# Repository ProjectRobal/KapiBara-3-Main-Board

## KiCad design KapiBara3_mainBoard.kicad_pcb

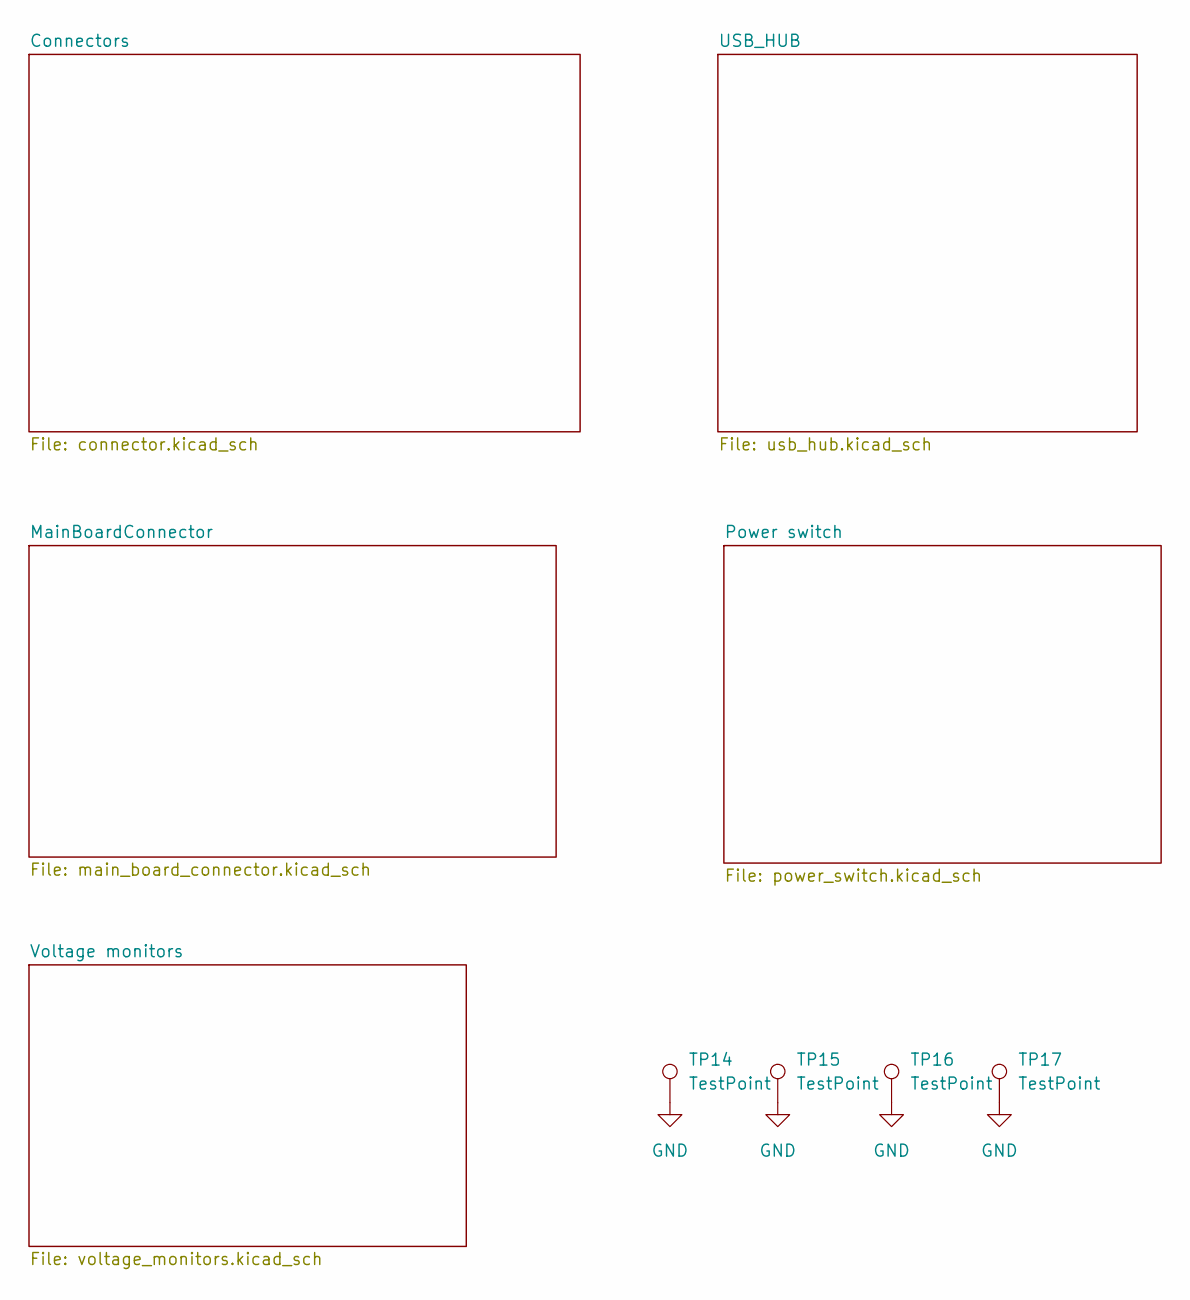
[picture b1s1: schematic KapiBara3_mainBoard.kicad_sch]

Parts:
TP14, TP15, TP16, TP17: TestPoint; TestPoint_Pad_D3.0mm

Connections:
GND: TP14.1, TP15.1, TP16.1, TP17.1; also elsewhere on the board

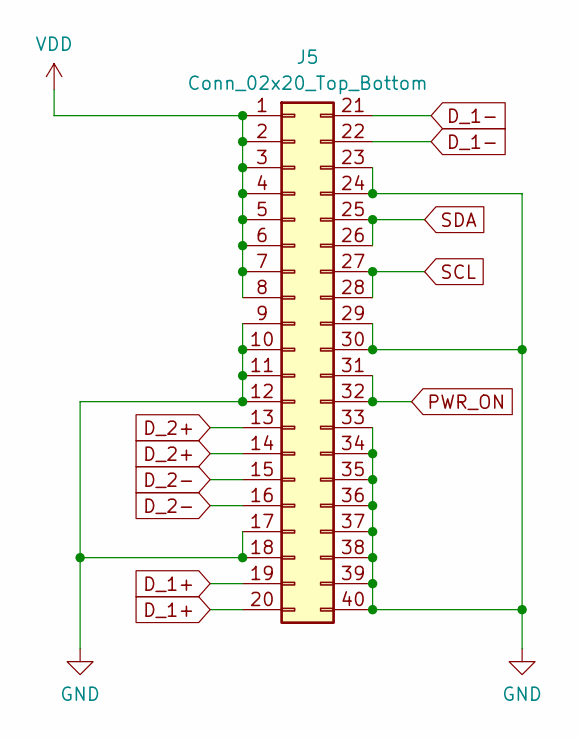
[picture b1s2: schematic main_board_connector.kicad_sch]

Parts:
J5: Conn_02x20_Top_Bottom; IDC-Header_2x20_P2.54mm_Vertical

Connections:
D_1+: J5.19, J5.20; also elsewhere on the board
D_1-: J5.21, J5.22; also elsewhere on the board
D_2+: J5.13, J5.14; also elsewhere on the board
D_2-: J5.15, J5.16; also elsewhere on the board
GND: J5.9, J5.10, J5.11, J5.12, J5.17, J5.18, J5.23, J5.24, J5.29, J5.30, J5.33, J5.34, J5.35, J5.36, J5.37, J5.38, J5.39, J5.40; also elsewhere on the board
PWR_ON: J5.31, J5.32; also elsewhere on the board
SCL: J5.27, J5.28; also elsewhere on the board
SDA: J5.25, J5.26; also elsewhere on the board
VDD: J5.1, J5.2, J5.3, J5.4, J5.5, J5.6, J5.7, J5.8; also elsewhere on the board

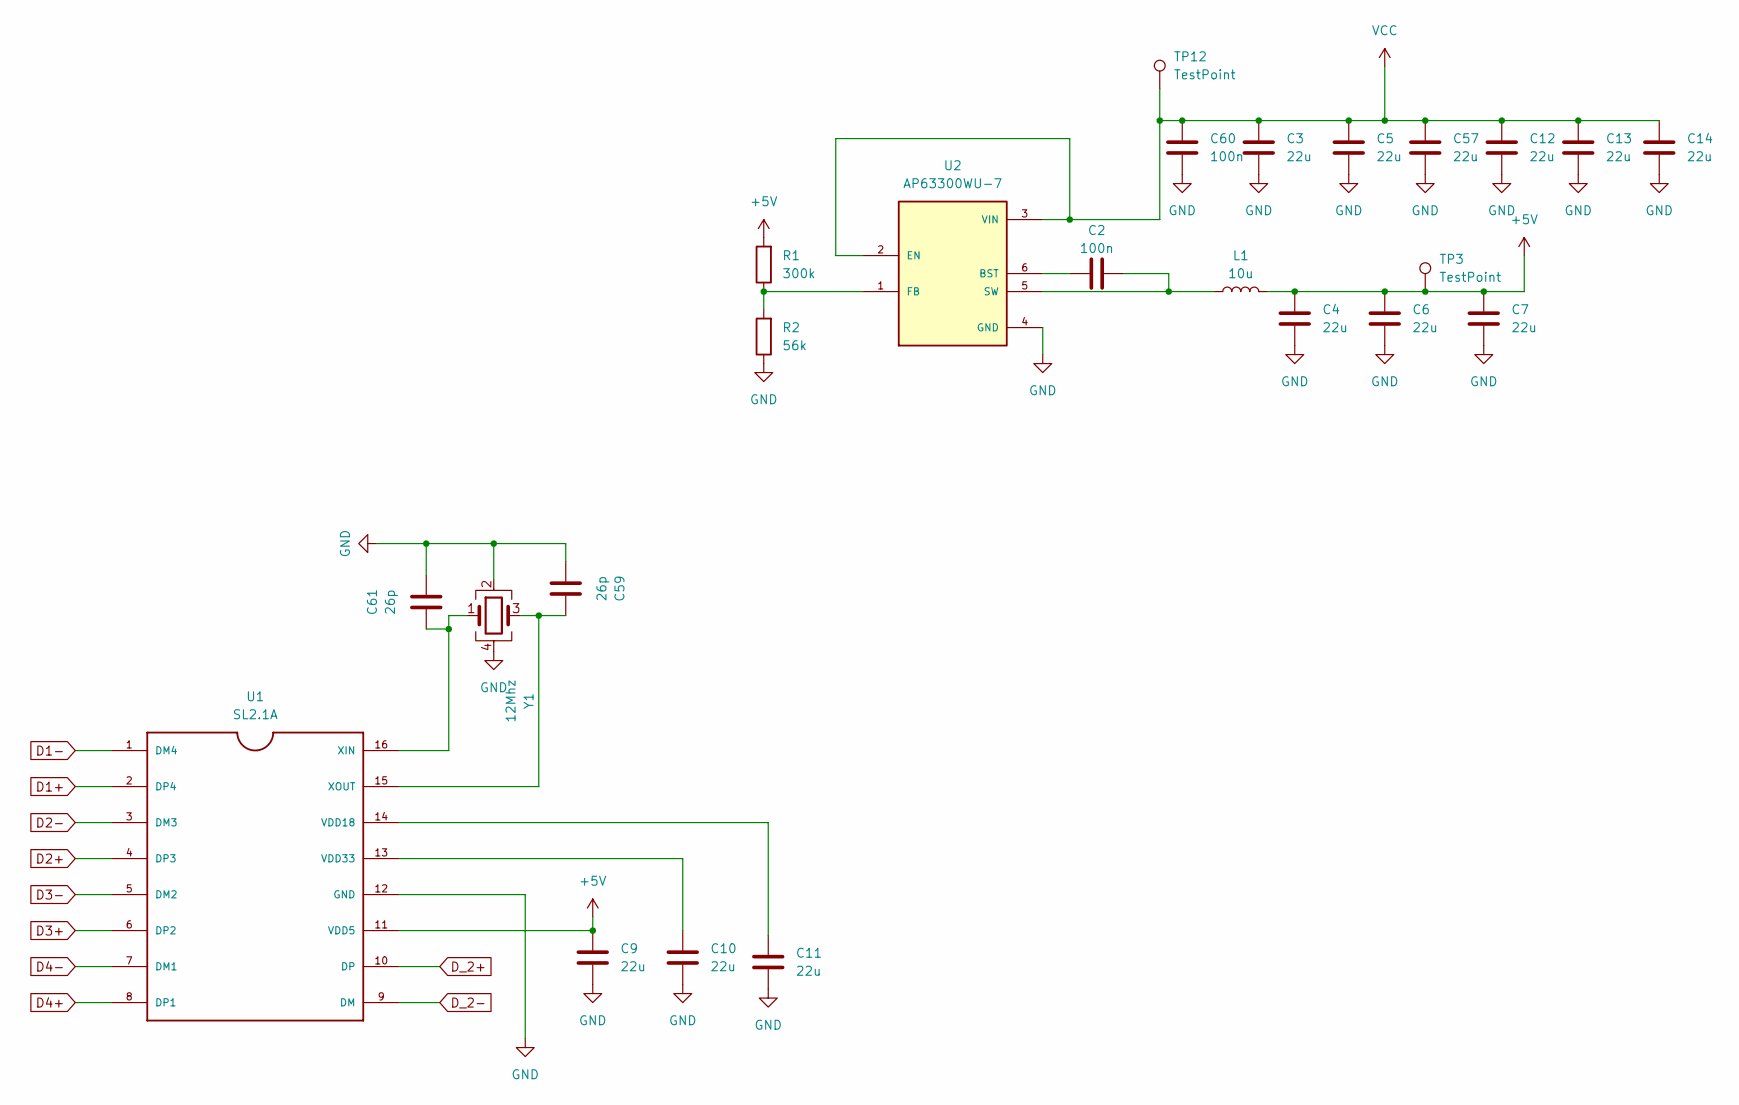
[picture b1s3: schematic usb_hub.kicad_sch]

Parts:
C2, C60: 100n; C_0603_1608Metric_Pad1.08x0.95mm_HandSolder
C3, C4, C5, C6, C7, C9, C10, C11, C12, C13, C14, C57: 22u; C_0805_2012Metric_Pad1.18x1.45mm_HandSolder
C59, C61: 26p; C_0603_1608Metric_Pad1.08x0.95mm_HandSolder
L1: 10u; L_Sunlord_SWPA5012S
R1: 300k; R_0603_1608Metric_Pad0.98x0.95mm_HandSolder
R2: 56k; R_0603_1608Metric_Pad0.98x0.95mm_HandSolder
TP3, TP12: TestPoint; TestPoint_Pad_1.5x1.5mm
U1: SL2.1A; SO16
U2: AP63300WU-7; SOT95P280X100-6N; PARTREV 2020-04-24
Y1: 12Mhz; Crystal_SMD_3225-4Pin_3.2x2.5mm_HandSoldering

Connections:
+5V: C4.1, C6.1, C7.1, C9.1, L1.2, R1.2, TP3.1, U1.11 (VDD5); also elsewhere on the board
D1+: U1.2 (DP4); also elsewhere on the board
D1-: U1.1 (DM4); also elsewhere on the board
D2+: U1.4 (DP3); also elsewhere on the board
D2-: U1.3 (DM3); also elsewhere on the board
D3+: U1.6 (DP2); also elsewhere on the board
D3-: U1.5 (DM2); also elsewhere on the board
D4+: U1.8 (DP1); also elsewhere on the board
D4-: U1.7 (DM1); also elsewhere on the board
D_2+: U1.10 (DP); also elsewhere on the board
D_2-: U1.9 (DM); also elsewhere on the board
GND: C3.2, C4.2, C5.2, C6.2, C7.2, C9.2, C10.2, C11.2, C12.2, C13.2, C14.2, C57.2, C59.1, C60.2, C61.1, R2.1, U1.12 (GND), U2.4 (GND), Y1.2, Y1.4; also elsewhere on the board
unnamed: C11.1, U1.14 (VDD18)
unnamed: C10.1, U1.13 (VDD33)
unnamed: C61.2, U1.16 (XIN), Y1.1
unnamed: C59.2, U1.15 (XOUT), Y1.3
unnamed: C2.1, U2.6 (BST)
unnamed: R1.1, R2.2, U2.1 (FB)
unnamed: C2.2, L1.1, U2.5 (SW)
VCC: C3.1, C5.1, C12.1, C13.1, C14.1, C57.1, C60.1, TP12.1, U2.2 (EN), U2.3 (VIN); also elsewhere on the board

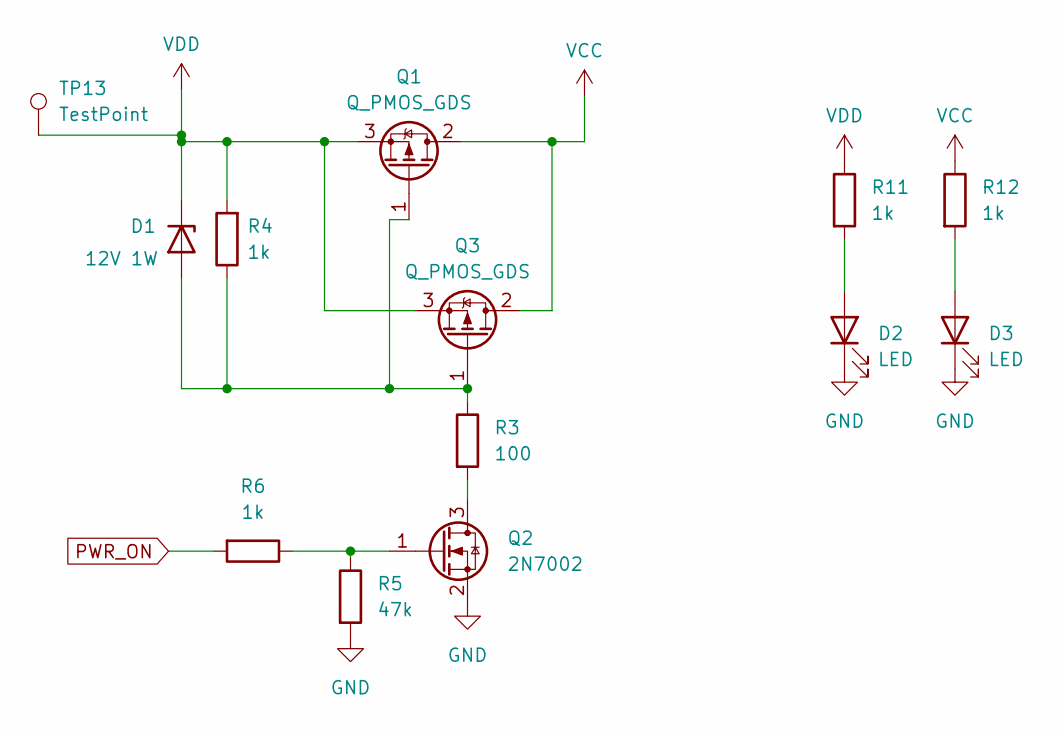
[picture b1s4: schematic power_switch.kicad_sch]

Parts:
D1: 12V 1W; D_SOD-123F
D2, D3: LED; LED_0805_2012Metric_Pad1.15x1.40mm_HandSolder
Q1, Q3: Q_PMOS_GDS; TO-252-2
Q2: 2N7002; SOT-23
R3: 100; R_0603_1608Metric
R4, R6, R11, R12: 1k; R_0603_1608Metric
R5: 47k; R_0603_1608Metric
TP13: TestPoint; TestPoint_Pad_1.5x1.5mm

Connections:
GND: D2.1 (K), D3.1 (K), Q2.2 (S), R5.2; also elsewhere on the board
unnamed: D1.2 (A), Q1.1 (G), Q3.1 (G), R3.1, R4.1
unnamed: D2.2 (A), R11.2
unnamed: D3.2 (A), R12.2
unnamed: Q2.3 (D), R3.2
unnamed: Q2.1 (G), R5.1, R6.1
PWR_ON: R6.2; also elsewhere on the board
VCC: Q1.2 (D), Q3.2 (D), R12.1; also elsewhere on the board
VDD: D1.1 (K), Q1.3 (S), Q3.3 (S), R4.2, R11.1, TP13.1; also elsewhere on the board

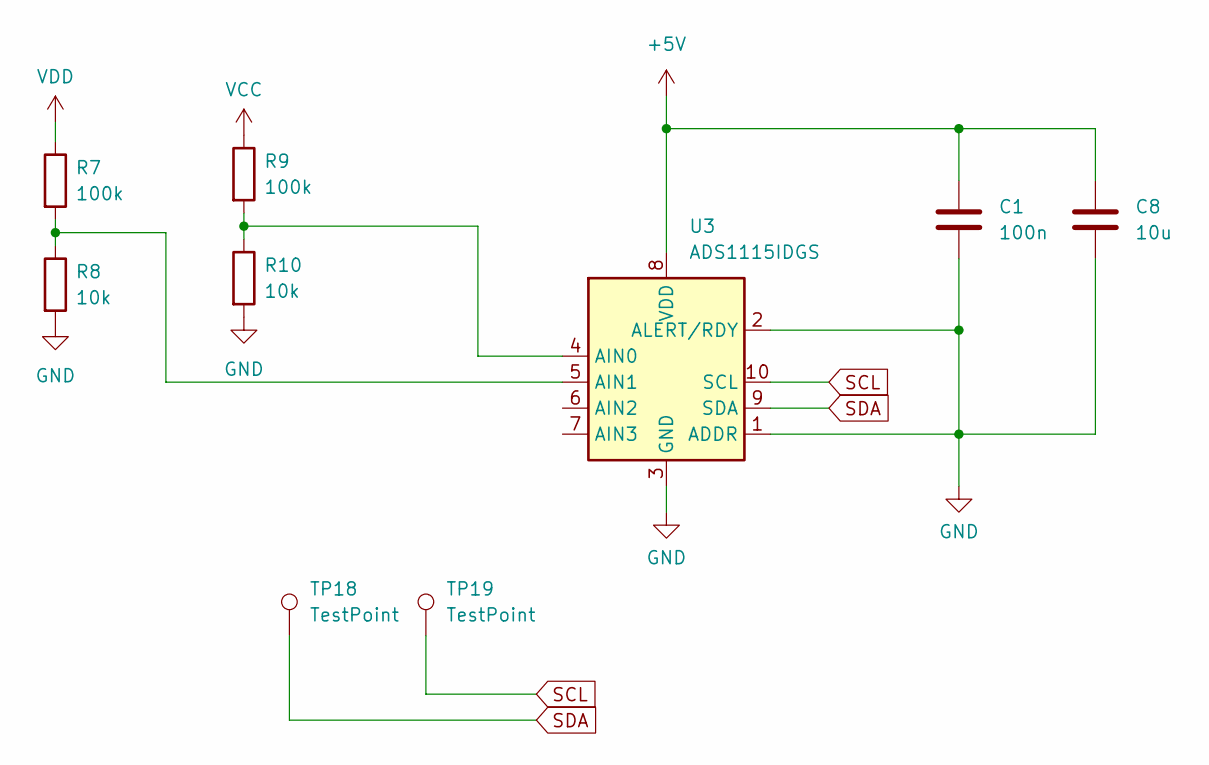
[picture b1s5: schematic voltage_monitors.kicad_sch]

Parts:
C1: 100n; C_0603_1608Metric_Pad1.08x0.95mm_HandSolder
C8: 10u; C_0603_1608Metric_Pad1.08x0.95mm_HandSolder
R7, R9: 100k; R_0603_1608Metric_Pad0.98x0.95mm_HandSolder
R8, R10: 10k; R_0603_1608Metric_Pad0.98x0.95mm_HandSolder
TP18, TP19: TestPoint; TestPoint_Pad_D1.5mm
U3: ADS1115IDGS; TSSOP-10_3x3mm_P0.5mm

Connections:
+5V: C1.1, C8.1, U3.8 (VDD); also elsewhere on the board
GND: C1.2, C8.2, R8.2, R10.2, U3.1 (ADDR), U3.2 (ALERT/RDY), U3.3 (GND); also elsewhere on the board
unnamed: R9.2, R10.1, U3.4 (AIN0)
unnamed: R7.2, R8.1, U3.5 (AIN1)
SCL: TP19.1, U3.10 (SCL); also elsewhere on the board
SDA: TP18.1, U3.9 (SDA); also elsewhere on the board
VCC: R9.1; also elsewhere on the board
VDD: R7.1; also elsewhere on the board

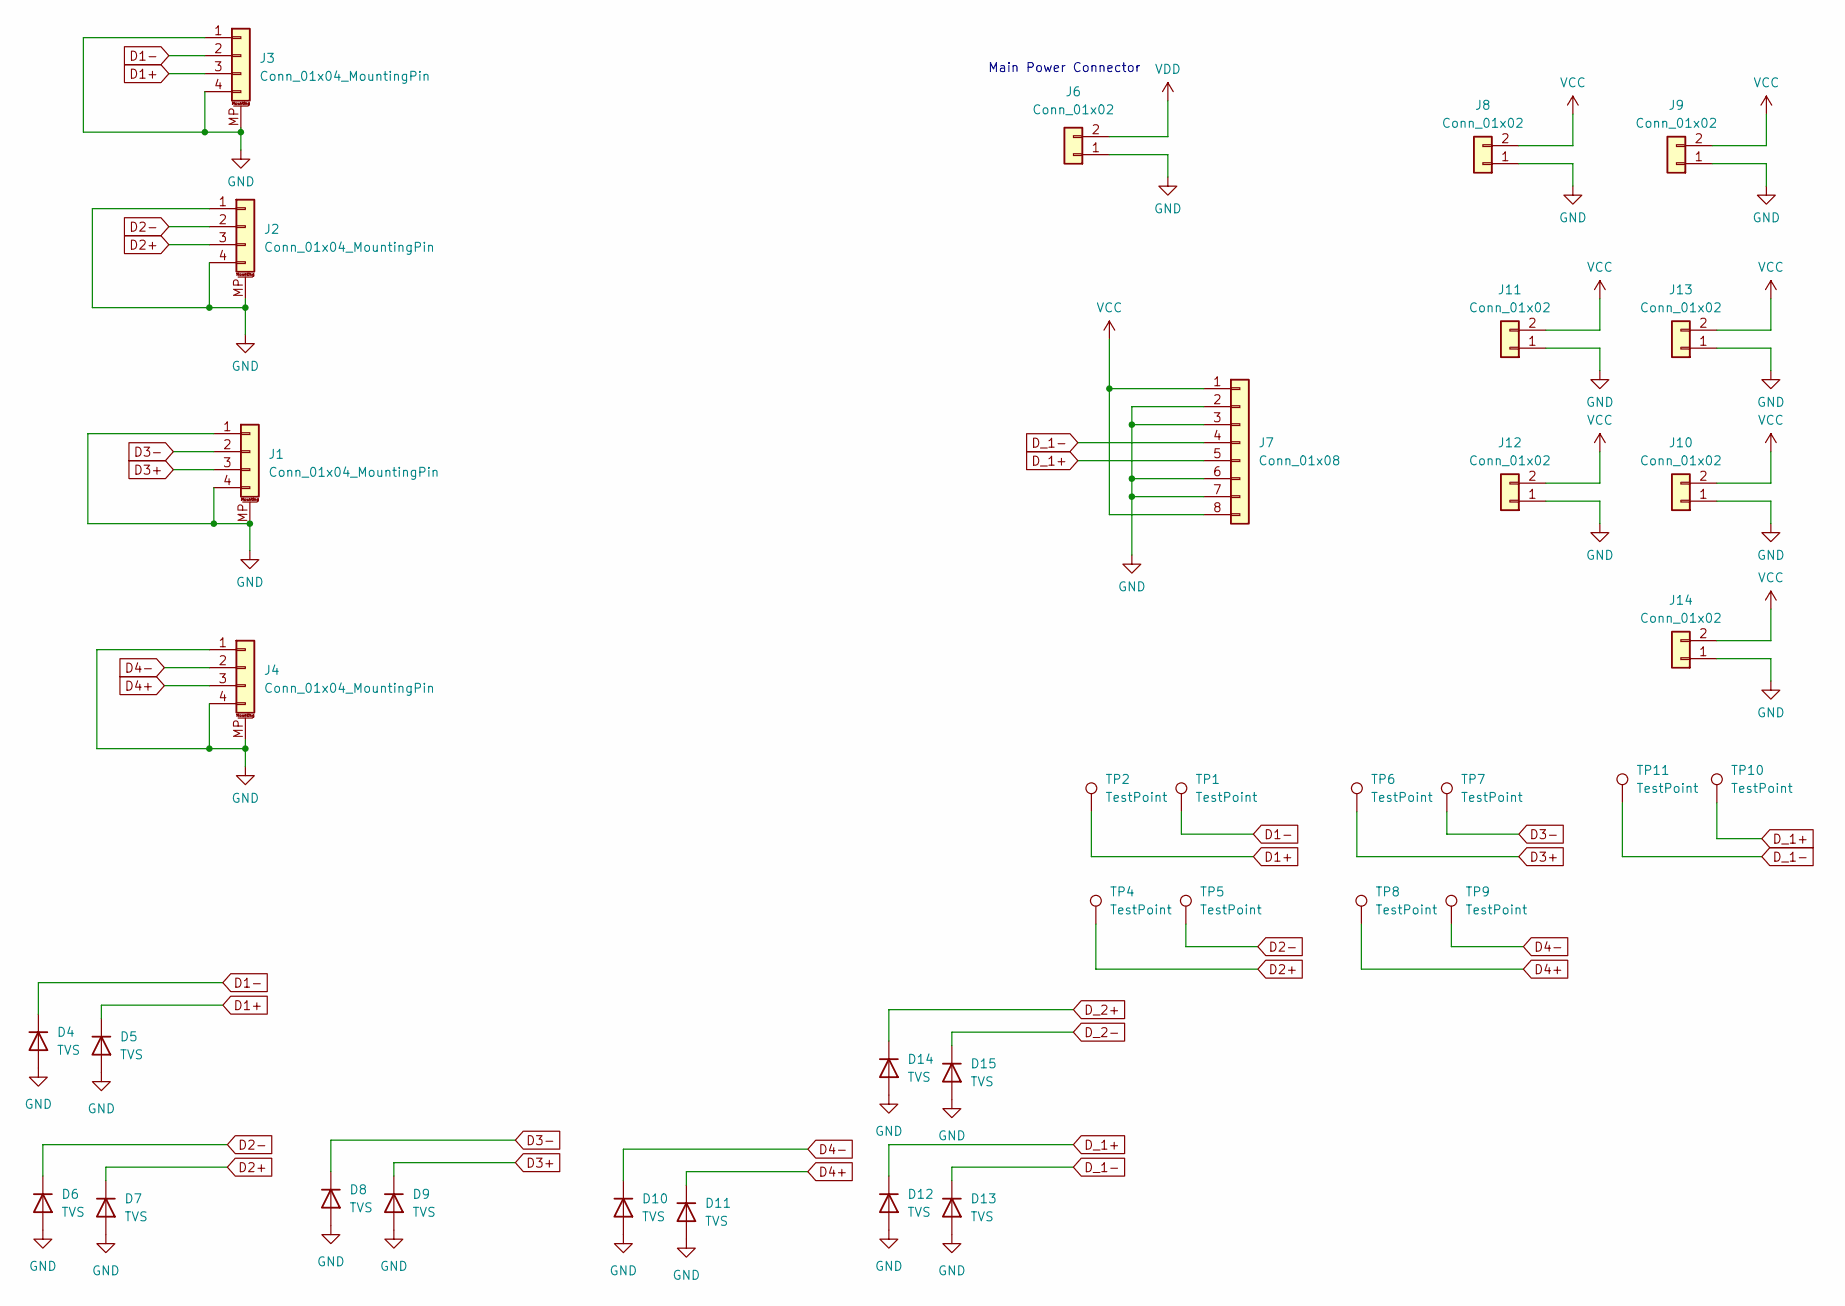
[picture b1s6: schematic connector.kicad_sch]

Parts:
D4, D5, D6, D7, D8, D9, D10, D11, D12, D13, D14, D15: TVS; D_SOD-323
J1, J2, J3, J4: Conn_01x04_MountingPin; Amphenol_F32Q-1A7x1-11004_1x04-1MP_P0.5mm_Horizontal
J6: Conn_01x02; AMASS_XT60-M_1x02_P7.20mm_Vertical
J7: Conn_01x08; PinHeader_1x08_P2.54mm_Vertical
J8, J9, J10, J11, J12, J13, J14: Conn_01x02; AMASS_XT30U-F_1x02_P5.0mm_Vertical
TP1, TP2, TP4, TP5, TP6, TP7, TP8, TP9, TP10, TP11: TestPoint; TestPoint_Pad_D1.5mm

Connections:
D1+: D5.1 (K), J3.3, TP2.1; also elsewhere on the board
D1-: D4.1 (K), J3.2, TP1.1; also elsewhere on the board
D2+: D7.1 (K), J2.3, TP4.1; also elsewhere on the board
D2-: D6.1 (K), J2.2, TP5.1; also elsewhere on the board
D3+: D9.1 (K), J1.3, TP6.1; also elsewhere on the board
D3-: D8.1 (K), J1.2, TP7.1; also elsewhere on the board
D4+: D11.1 (K), J4.3, TP8.1; also elsewhere on the board
D4-: D10.1 (K), J4.2, TP9.1; also elsewhere on the board
D_1+: D12.1 (K), J7.5, TP10.1; also elsewhere on the board
D_1-: D13.1 (K), J7.4, TP11.1; also elsewhere on the board
D_2+: D14.1 (K); also elsewhere on the board
D_2-: D15.1 (K); also elsewhere on the board
GND: D4.2 (A), D5.2 (A), D6.2 (A), D7.2 (A), D8.2 (A), D9.2 (A), D10.2 (A), D11.2 (A), D12.2 (A), D13.2 (A), D14.2 (A), D15.2 (A), J1.1, J1.4, J1.MP (MountPin), J2.1, J2.4, J2.MP (MountPin), J3.1, J3.4, J3.MP (MountPin), J4.1, J4.4, J4.MP (MountPin), J6.1, J7.2, J7.3, J7.6, J7.7, J8.1, J9.1, J10.1, J11.1, J12.1, J13.1, J14.1; also elsewhere on the board
VCC: J7.1, J7.8, J8.2, J9.2, J10.2, J11.2, J12.2, J13.2, J14.2; also elsewhere on the board
VDD: J6.2; also elsewhere on the board

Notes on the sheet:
Main Power Connector

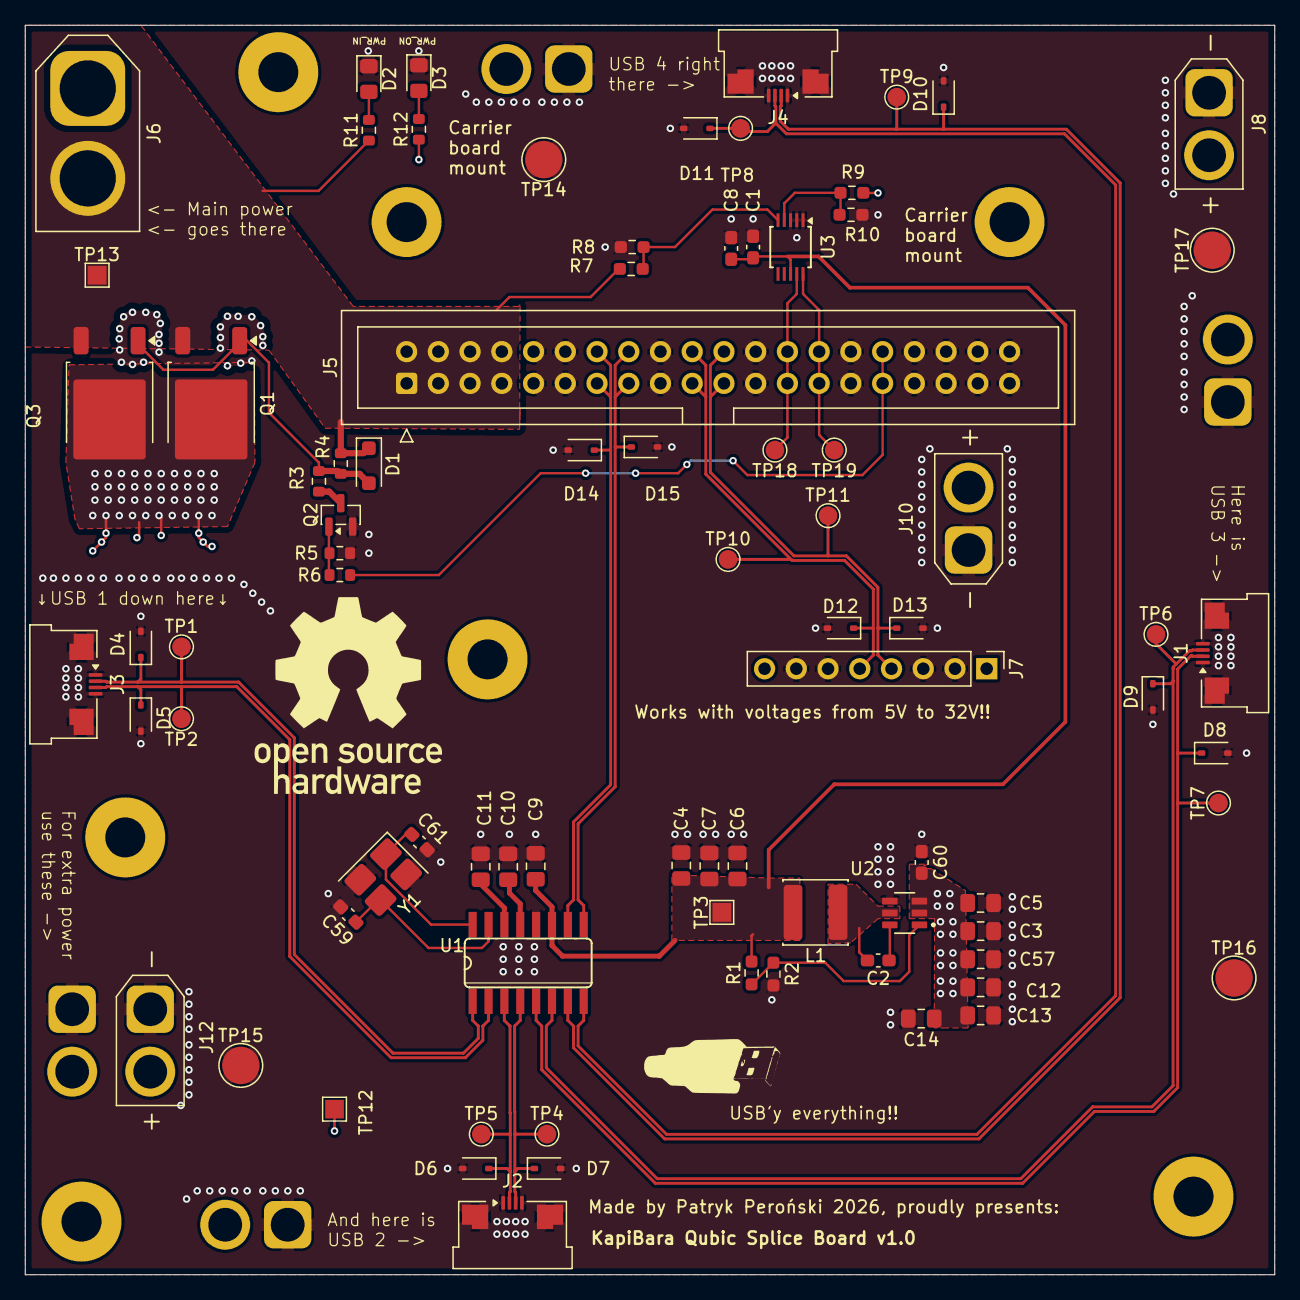
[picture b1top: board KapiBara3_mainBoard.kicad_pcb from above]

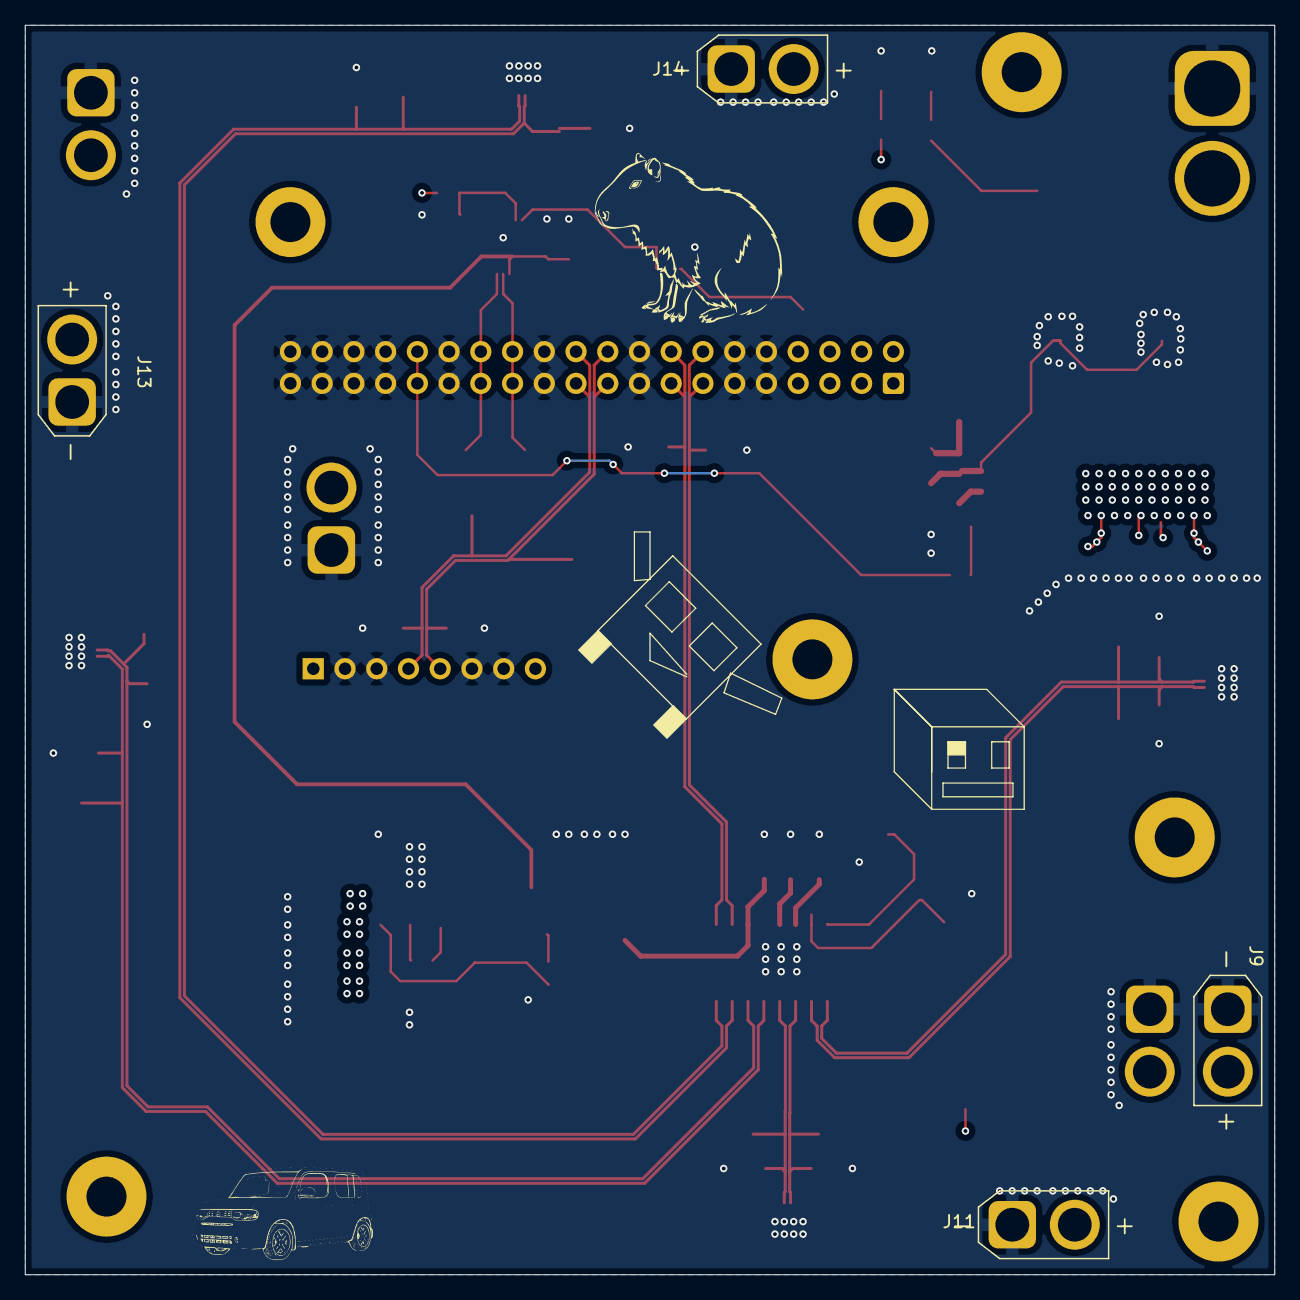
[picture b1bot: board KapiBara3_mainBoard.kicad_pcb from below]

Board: 4 copper layers, 100.0 x 100.0 mm, 86 parts (4 on the bottom side), 33 nets.

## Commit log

2026-01-12 Added mouting holes
2026-01-16 I need to think what else to add
2026-01-20 Added some offsets to board outlines
2026-01-25 I have shrinken down the board
2026-01-29 Final design
